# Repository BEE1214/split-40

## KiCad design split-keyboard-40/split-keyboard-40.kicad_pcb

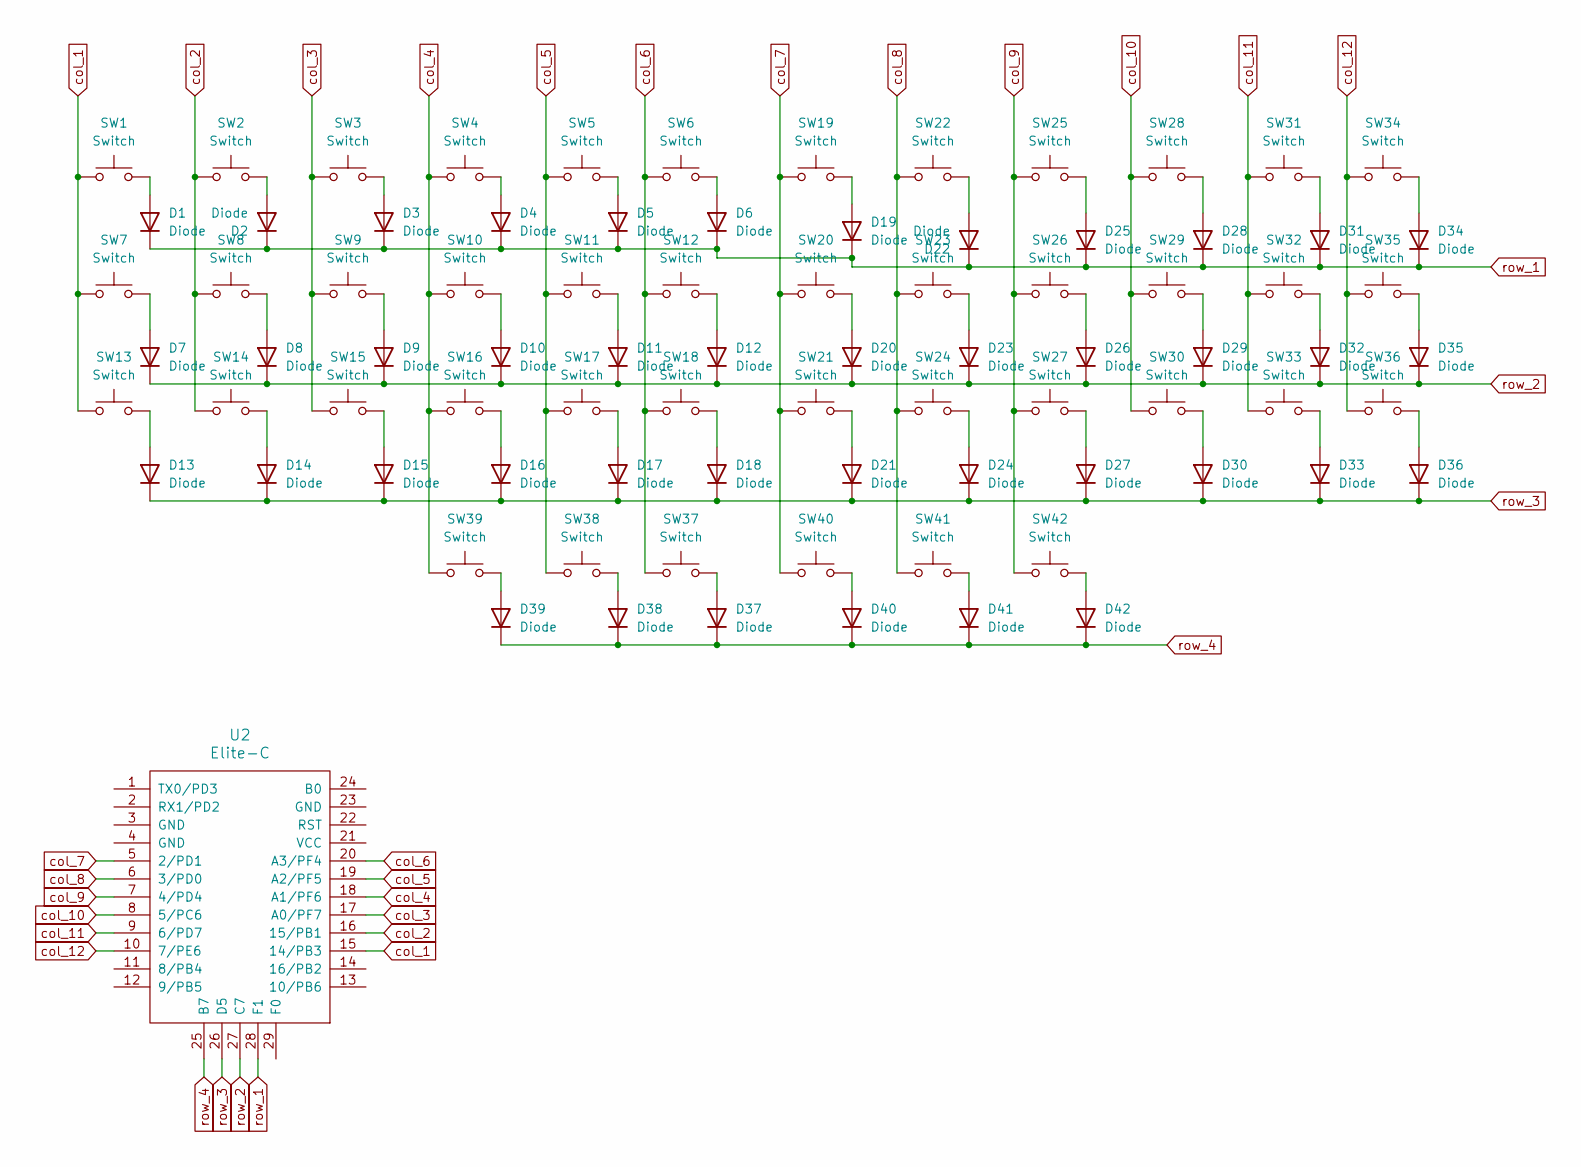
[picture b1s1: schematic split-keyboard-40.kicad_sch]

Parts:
D1, D2, D3, D4, D5, D6, D7, D8, D9, D10, D11, D12, D13, D14, D15, D16, D17, D18, D19, D20, D21, D22, D23, D24, D25, D26, D27, D28, D29, D30, D31, D32, D33, D34, D35, D36, D37, D38, D39, D40, D41, D42: Diode; Diode_SOD-123
SW1, SW2, SW3, SW4, SW5, SW6, SW7, SW8, SW9, SW10, SW11, SW12, SW13, SW14, SW15, SW16, SW17, SW18, SW19, SW20, SW21, SW22, SW23, SW24, SW25, SW26, SW27, SW28, SW29, SW30, SW31, SW32, SW33, SW34, SW35, SW36, SW37, SW38, SW39, SW40, SW41, SW42: Switch; Hotswap_MX_1.00u
U2: Elite-C

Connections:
unnamed: D1.2 (A), SW1.2
unnamed: D2.2 (A), SW2.2
unnamed: D3.2 (A), SW3.2
unnamed: D4.2 (A), SW4.2
unnamed: D5.2 (A), SW5.2
unnamed: D6.2 (A), SW6.2
unnamed: D7.2 (A), SW7.2
unnamed: D8.2 (A), SW8.2
unnamed: D9.2 (A), SW9.2
unnamed: D10.2 (A), SW10.2
unnamed: D11.2 (A), SW11.2
unnamed: D12.2 (A), SW12.2
unnamed: D13.2 (A), SW13.2
unnamed: D14.2 (A), SW14.2
unnamed: D15.2 (A), SW15.2
unnamed: D16.2 (A), SW16.2
unnamed: D17.2 (A), SW17.2
unnamed: D18.2 (A), SW18.2
unnamed: D19.2 (A), SW19.2
unnamed: D20.2 (A), SW20.2
unnamed: D21.2 (A), SW21.2
unnamed: D22.2 (A), SW22.2
unnamed: D23.2 (A), SW23.2
unnamed: D24.2 (A), SW24.2
unnamed: D25.2 (A), SW25.2
unnamed: D26.2 (A), SW26.2
unnamed: D27.2 (A), SW27.2
unnamed: D28.2 (A), SW28.2
unnamed: D29.2 (A), SW29.2
unnamed: D30.2 (A), SW30.2
unnamed: D31.2 (A), SW31.2
unnamed: D32.2 (A), SW32.2
unnamed: D33.2 (A), SW33.2
unnamed: D34.2 (A), SW34.2
unnamed: D35.2 (A), SW35.2
unnamed: D36.2 (A), SW36.2
unnamed: D37.2 (A), SW37.2
unnamed: D38.2 (A), SW38.2
unnamed: D39.2 (A), SW39.2
unnamed: D40.2 (A), SW40.2
unnamed: D41.2 (A), SW41.2
unnamed: D42.2 (A), SW42.2
col_1: SW1.1, SW7.1, SW13.1, U2.15 (14/PB3)
col_2: SW2.1, SW8.1, SW14.1, U2.16 (15/PB1)
col_3: SW3.1, SW9.1, SW15.1, U2.17 (A0/PF7)
col_4: SW4.1, SW10.1, SW16.1, SW39.1, U2.18 (A1/PF6)
col_5: SW5.1, SW11.1, SW17.1, SW38.1, U2.19 (A2/PF5)
col_6: SW6.1, SW12.1, SW18.1, SW37.1, U2.20 (A3/PF4)
col_7: SW19.1, SW20.1, SW21.1, SW40.1, U2.5 (2/PD1)
col_8: SW22.1, SW23.1, SW24.1, SW41.1, U2.6 (3/PD0)
col_9: SW25.1, SW26.1, SW27.1, SW42.1, U2.7 (4/PD4)
col_10: SW28.1, SW29.1, SW30.1, U2.8 (5/PC6)
col_11: SW31.1, SW32.1, SW33.1, U2.9 (6/PD7)
col_12: SW34.1, SW35.1, SW36.1, U2.10 (7/PE6)
row_1: D1.1 (K), D2.1 (K), D3.1 (K), D4.1 (K), D5.1 (K), D6.1 (K), D19.1 (K), D22.1 (K), D25.1 (K), D28.1 (K), D31.1 (K), D34.1 (K), U2.28 (F1)
row_2: D7.1 (K), D8.1 (K), D9.1 (K), D10.1 (K), D11.1 (K), D12.1 (K), D20.1 (K), D23.1 (K), D26.1 (K), D29.1 (K), D32.1 (K), D35.1 (K), U2.27 (C7)
row_3: D13.1 (K), D14.1 (K), D15.1 (K), D16.1 (K), D17.1 (K), D18.1 (K), D21.1 (K), D24.1 (K), D27.1 (K), D30.1 (K), D33.1 (K), D36.1 (K), U2.26 (D5)
row_4: D37.1 (K), D38.1 (K), D39.1 (K), D40.1 (K), D41.1 (K), D42.1 (K), U2.25 (B7)

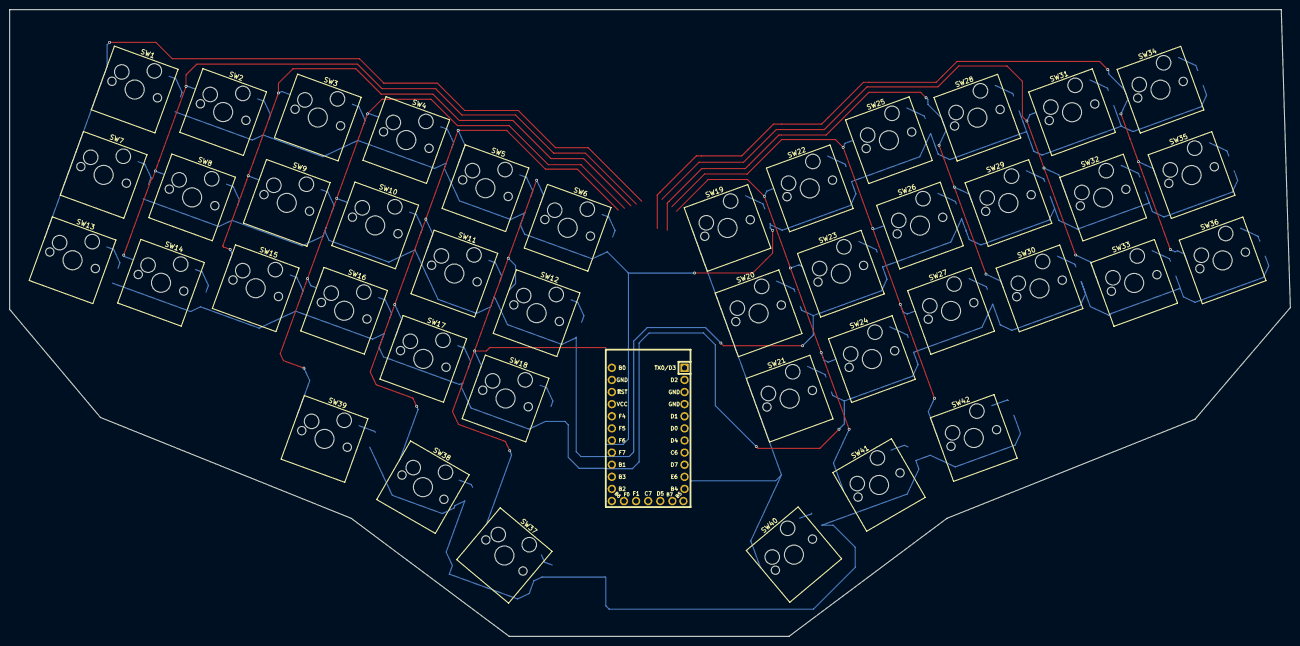
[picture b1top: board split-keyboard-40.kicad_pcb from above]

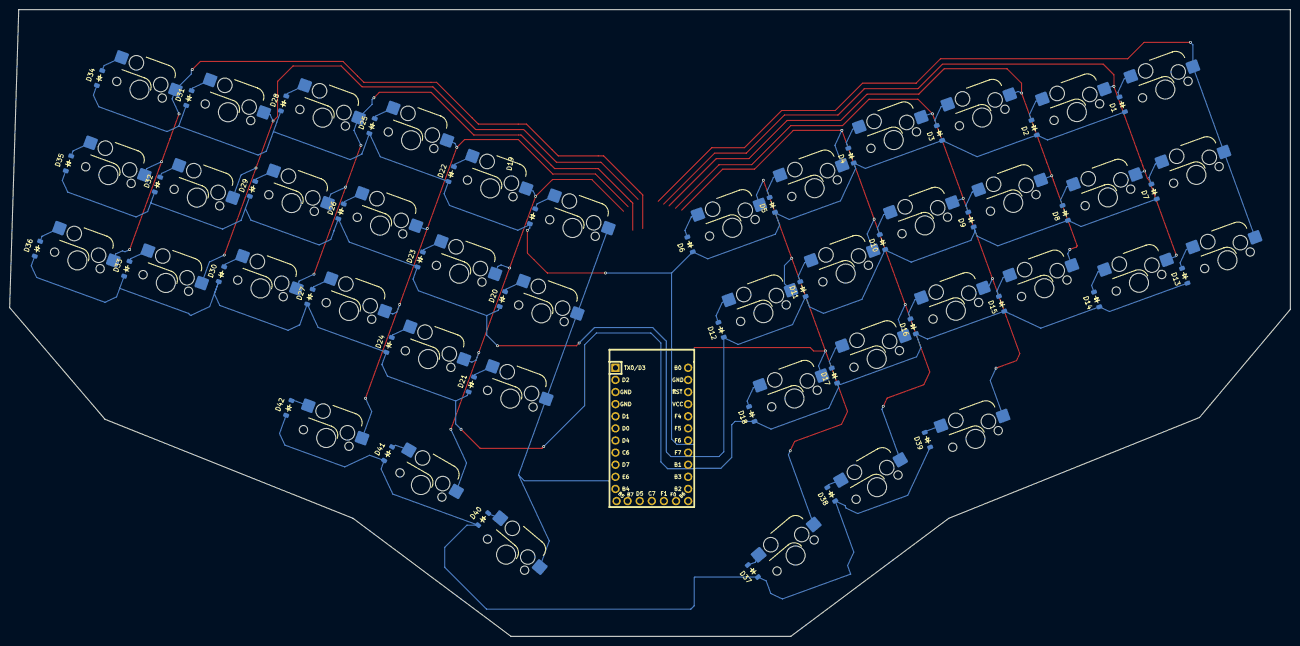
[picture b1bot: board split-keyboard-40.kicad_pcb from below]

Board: 2 copper layers, 268.6 x 131.4 mm, 85 parts (43 on the bottom side), 58 nets.

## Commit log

2024-05-20 init
2024-05-21 basic routing
2024-05-26 keyboard layout
2024-07-01 routing of both sides, rotation
2024-07-01 few rows
2024-09-01 ergogen layout + elite-c
2024-09-14 updated board
2024-09-14 ergogen
2024-09-14 add ben vallacks ergogen
2024-09-14 ergogen as submodule
2024-09-28 remove zip files
2024-09-29 pcb outline
